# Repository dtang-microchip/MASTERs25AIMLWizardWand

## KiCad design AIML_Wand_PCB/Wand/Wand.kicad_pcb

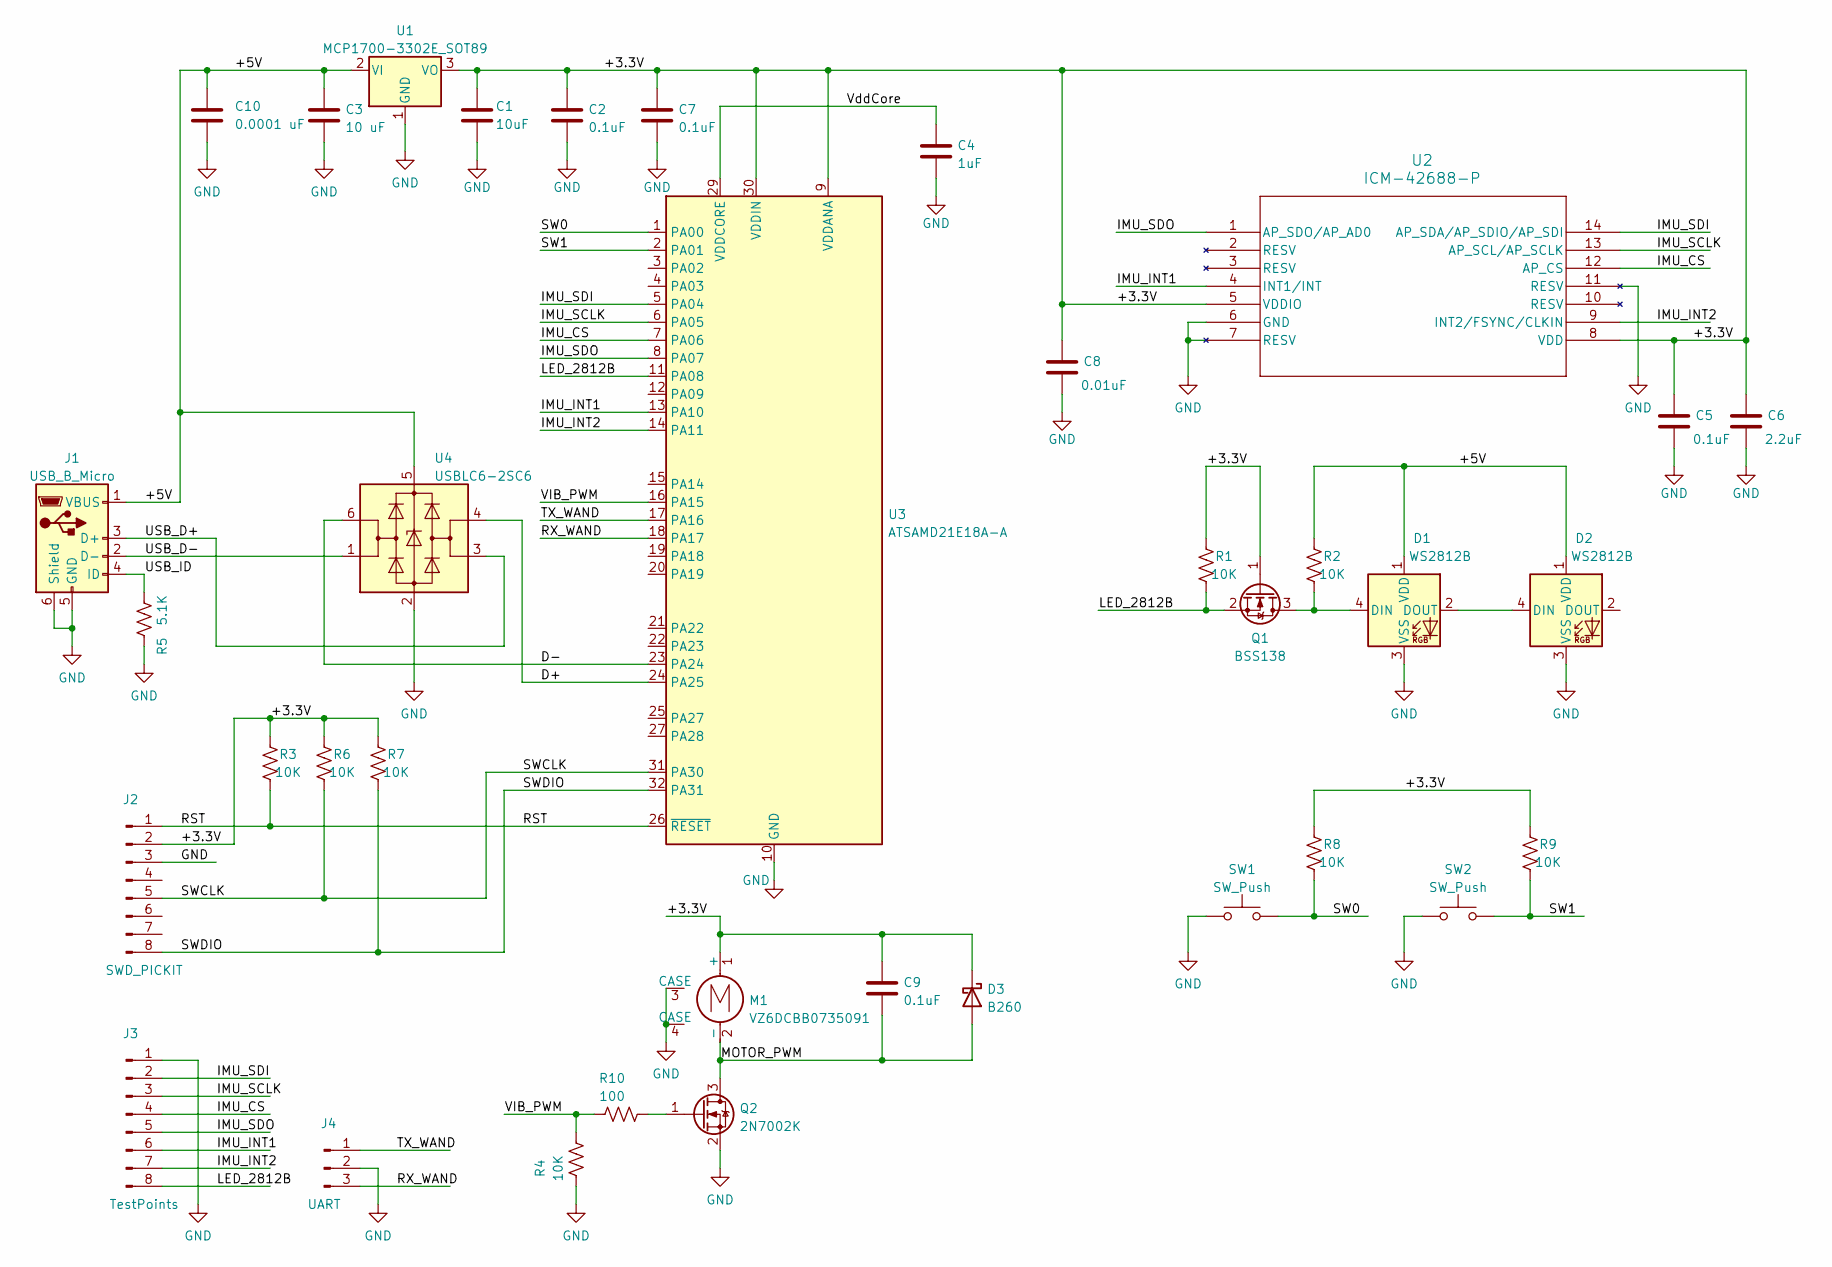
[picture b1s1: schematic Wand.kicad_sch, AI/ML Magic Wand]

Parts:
C1: 10uF; C_0805_2012Metric_Pad1.18x1.45mm_HandSolder
C2, C7, C9: 0.1uF; C_0805_2012Metric_Pad1.18x1.45mm_HandSolder
C3: 10 uF; C_0805_2012Metric_Pad1.18x1.45mm_HandSolder
C4: 1uF; C_0805_2012Metric_Pad1.18x1.45mm_HandSolder
C5: 0.1uF; C_0603_1608Metric_Pad1.08x0.95mm_HandSolder
C6: 2.2uF; C_0603_1608Metric_Pad1.08x0.95mm_HandSolder
C8: 0.01uF; C_0603_1608Metric_Pad1.08x0.95mm_HandSolder
C10: 0.0001 uF; C_0805_2012Metric_Pad1.18x1.45mm_HandSolder
D1, D2: WS2812B; LED_WS2812B_PLCC4_5.0x5.0mm_P3.2mm
D3: B260; D_SMB
J1: USB_B_Micro; USB_Micro-B_Wuerth_629105150521_CircularHoles
J2: SWD_PICKIT; PinHeader_1x08_P2.54mm_Vertical
J3: TestPoints; PinHeader_2x04_P2.54mm_Vertical
J4: UART; PinHeader_1x03_P2.54mm_Vertical
M1: VZ6DCBB0735091; VZ6DC_VIB
Q1: BSS138; SOT-23
Q2: 2N7002K; SOT-23
R1, R2, R3, R4, R6, R7, R8, R9: 10K; R_0805_2012Metric_Pad1.20x1.40mm_HandSolder
R5: 5.1K; R_0805_2012Metric_Pad1.20x1.40mm_HandSolder
R10: 100; R_0805_2012Metric_Pad1.20x1.40mm_HandSolder
SW1, SW2: SW_Push; SW_SPST_B3SL-1022P
U1: MCP1700-3302E_SOT89; SOT-89-3
U2: ICM-42688-P; LGA14_2P5X3X0P91_TDK
U3: ATSAMD21E18A-A; TQFP-32_7x7mm_P0.8mm
U4: USBLC6-2SC6; SOT-23-6

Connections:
/+3.3V: C1.1, C2.1, C5.1, C6.1, C7.1, C8.1, C9.1, D3.1 (K), J2.2, M1.1 (+), Q1.1 (G), R1.2, R3.2, R6.2, R7.2, R8.2, R9.2, U1.3 (VO), U2.5 (VDDIO), U2.8 (VDD), U3.9 (VDDANA), U3.30 (VDDIN)
/+5V: C3.1, C10.1, D1.1 (VDD), D2.1 (VDD), J1.1 (VBUS), R2.2, U1.2 (VI), U4.5 (VBUS)
/D+: U3.24 (PA25), U4.4 (I/O2)
/D-: U3.23 (PA24), U4.6 (I/O1)
/IMU_CS: J3.4, U2.12 (AP_CS), U3.7 (PA06)
/IMU_INT1: J3.6, U2.4 (INT1/INT), U3.13 (PA10)
/IMU_INT2: J3.7, U2.9 (INT2/FSYNC/CLKIN), U3.14 (PA11)
/IMU_SCLK: J3.3, U2.13 (AP_SCL/AP_SCLK), U3.6 (PA05)
/IMU_SDI: J3.2, U2.14 (AP_SDA/AP_SDIO/AP_SDI), U3.5 (PA04)
/IMU_SDO: J3.5, U2.1 (AP_SDO/AP_AD0), U3.8 (PA07)
/LED_2812B: J3.8, Q1.2 (S), R1.1, U3.11 (PA08)
/MOTOR_PWM: C9.2, D3.2 (A), M1.2 (-), Q2.3 (D)
/RST: J2.1, R3.1, U3.26 (~RESET)
/RX_WAND: J4.3, U3.18 (PA17)
/SW0: R8.1, SW1.2, U3.1 (PA00)
/SW1: R9.1, SW2.2, U3.2 (PA01)
/SWCLK: J2.5, R6.1, U3.31 (PA30)
/SWDIO: J2.8, R7.1, U3.32 (PA31)
/TX_WAND: J4.1, U3.17 (PA16)
/USB_D+: J1.3 (D+), U4.3 (I/O2)
/USB_D-: J1.2 (D-), U4.1 (I/O1)
/USB_ID: J1.4 (ID), R5.2
/VIB_PWM: R4.1, R10.2, U3.16 (PA15)
/VddCore: C4.1, U3.29 (VDDCORE)
GND: C1.2, C2.2, C3.2, C4.2, C5.2, C6.2, C7.2, C8.2, C10.2, D1.3 (VSS), D2.3 (VSS), J1.5 (GND), J1.6 (Shield), J2.3, J3.1, J4.2, M1.3 (CASE), M1.4 (CASE), Q2.2 (S), R4.2, R5.1, SW1.1, SW2.1, U1.1 (GND), U2.6 (GND), U2.7 (RESV), U2.11 (RESV), U3.10 (GND), U3.28 (GND), U4.2 (GND)
unnamed: D1.4 (DIN), Q1.3 (D), R2.1
unnamed: D1.2 (DOUT), D2.4 (DIN)
unnamed: Q2.1 (G), R10.1

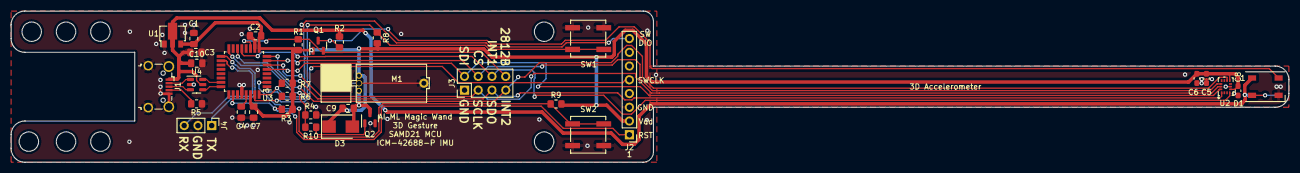
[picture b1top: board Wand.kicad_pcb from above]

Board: 2 copper layers, 236.2 x 27.9 mm, 36 parts (1 on the bottom side), 28 nets.

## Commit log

2025-03-11 Add initial .gitignore
2025-03-11 Initial MPLABX Project
2025-03-11 this is a test , delete later
2025-03-11 Initial MCC Configuration for USB and XPRO BSP
2025-03-11 Updated .gitignore location
2025-03-11 Add MCC Generated files for USB and XPRO BSP
2025-03-18 Change app.c/h to CDC_UART.c/h
2025-03-18 things added - DMA - TCC0 and TC3 for ws2812 conntrol -TC4 as a timer - added files ws2812.c and ws2812.h -created a state machine that will cycle through it's states with the push of the button in t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
2025-03-18 Fixup Commit: Updates and Fixes for ws2812
2025-03-18 Update USBCDC to accept incoming buffer and send via API command
2025-03-18 Remove XSAMD21XPRO BSP
2025-04-16 Add ICM426xx driver folder
2025-04-16 Add BMI160 driver folder
2025-05-05 Add IMU abstraction layers and sensor API
2025-05-05 Add SERCOM0 as SPI for and and PA10 as EXTINT for IMU communications
2025-05-05 pull newly added files into MPLAB Project for IMU drivers
2025-05-05 Add ringbuffer API
